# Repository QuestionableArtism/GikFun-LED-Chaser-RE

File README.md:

# GikFun-LED-Chaser-RE

### Purpose
I am testing to make sure my process of making schematic and then PCB and such is working.  I should be able to just use the solder practice kit 1:1 and it should work the same.

### Files:
The schematic, netlist, and PCB are all here.  I will update the ReadMe if it works.  I'm waiting on the order from osh park rn.

The one modification is that I am using a different power socket since the one they use is really obscure and I only found it in one place.  This one is meant to use the following receptacle:  https://www.mouser.com/ProductDetail/710-694106301002

Can be powered with any 2.1 x 5.5 5V DC barrel.

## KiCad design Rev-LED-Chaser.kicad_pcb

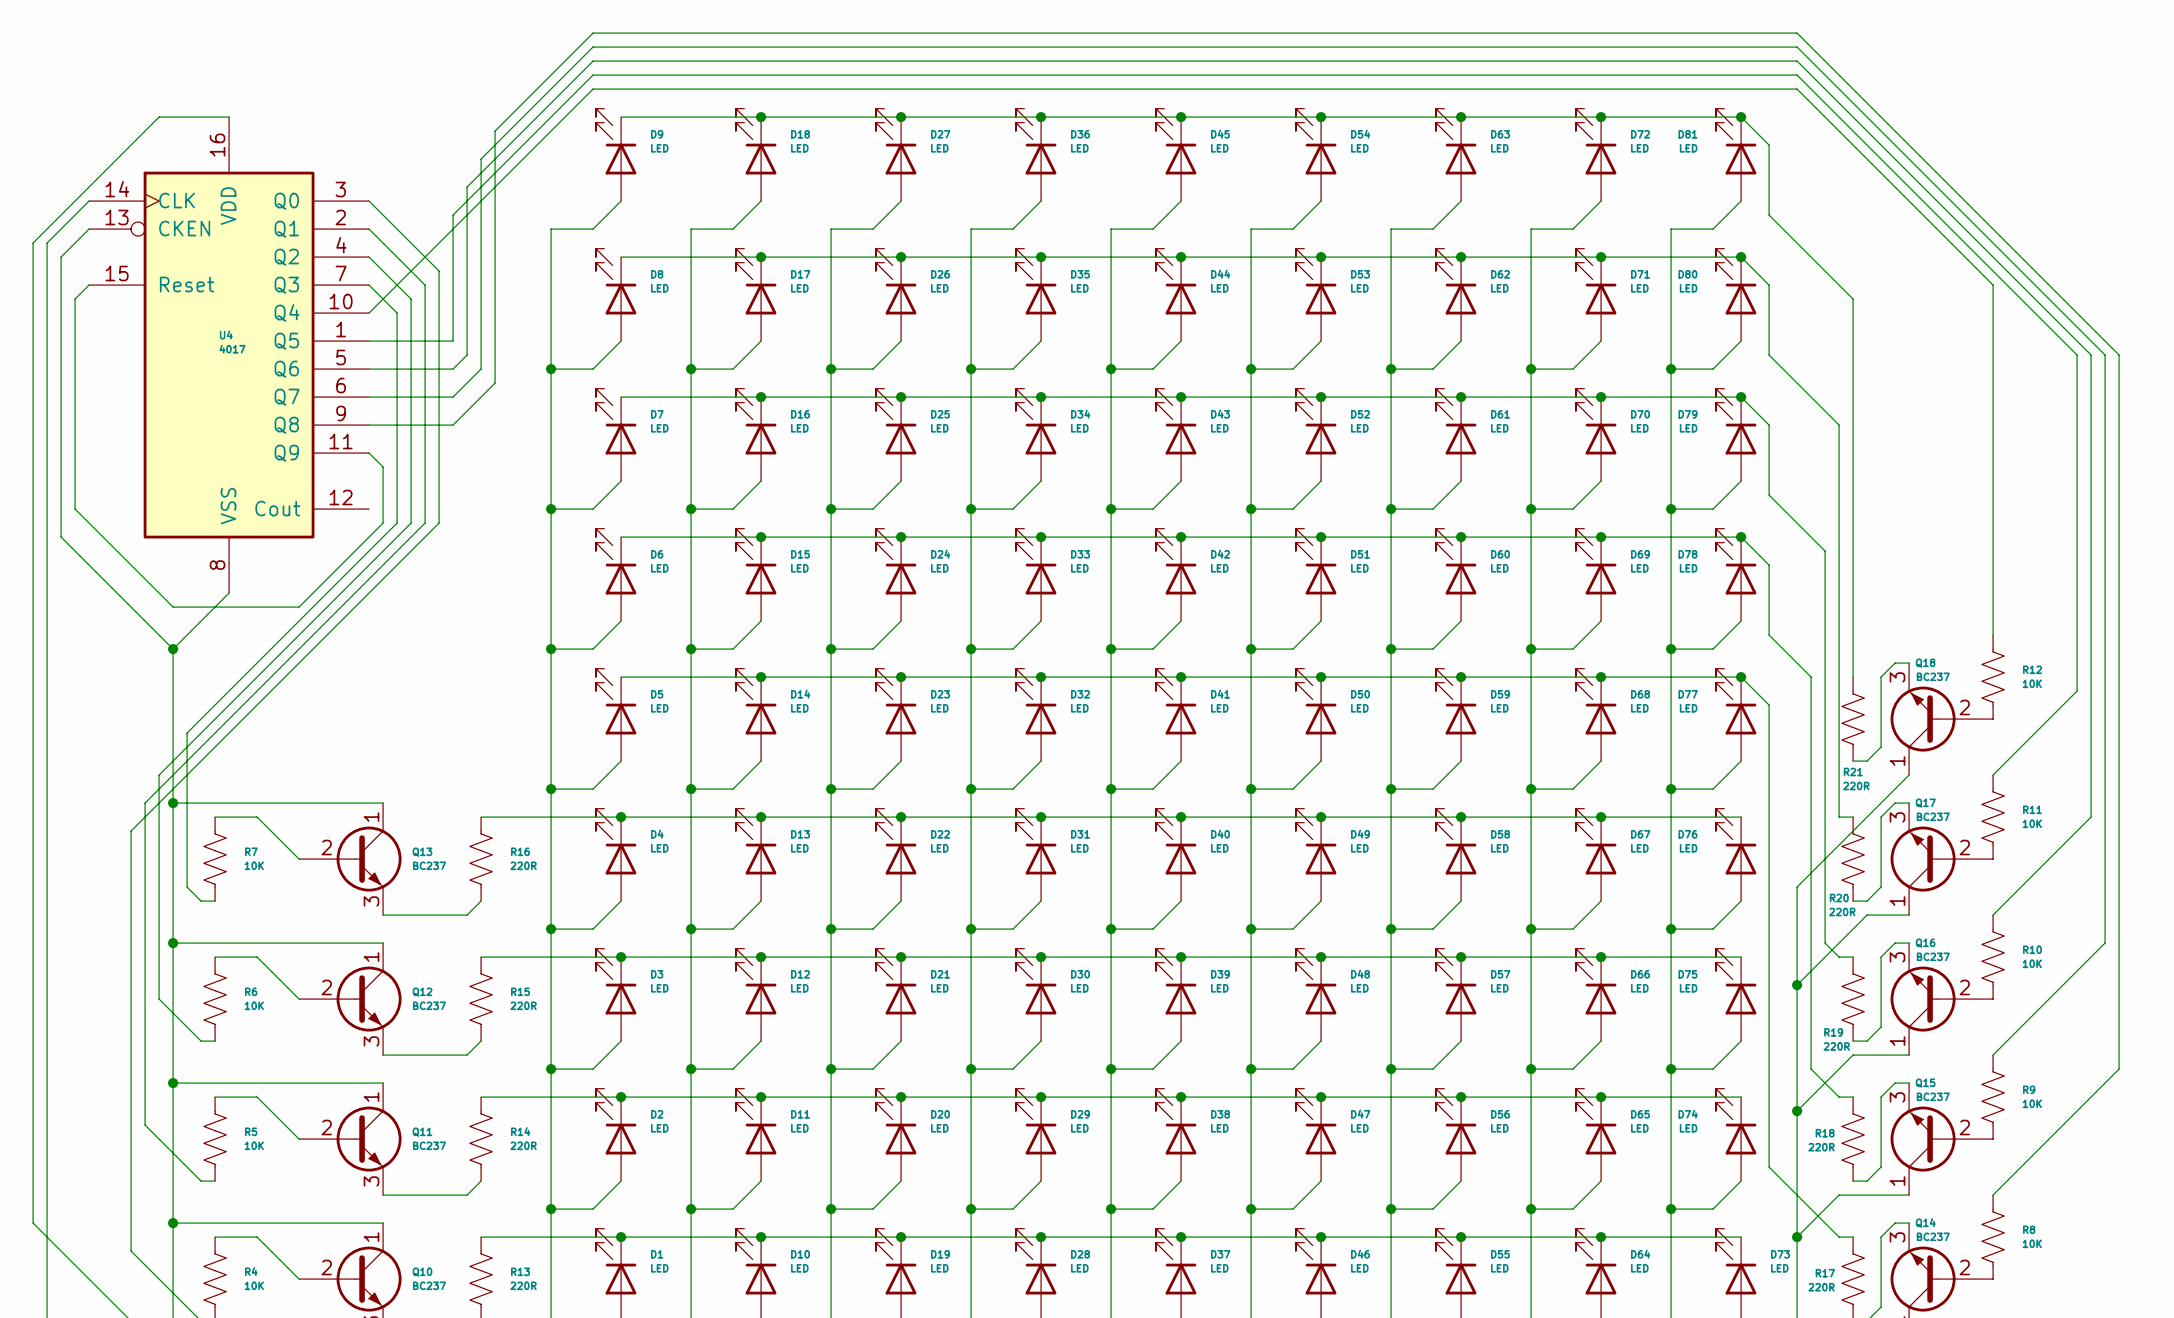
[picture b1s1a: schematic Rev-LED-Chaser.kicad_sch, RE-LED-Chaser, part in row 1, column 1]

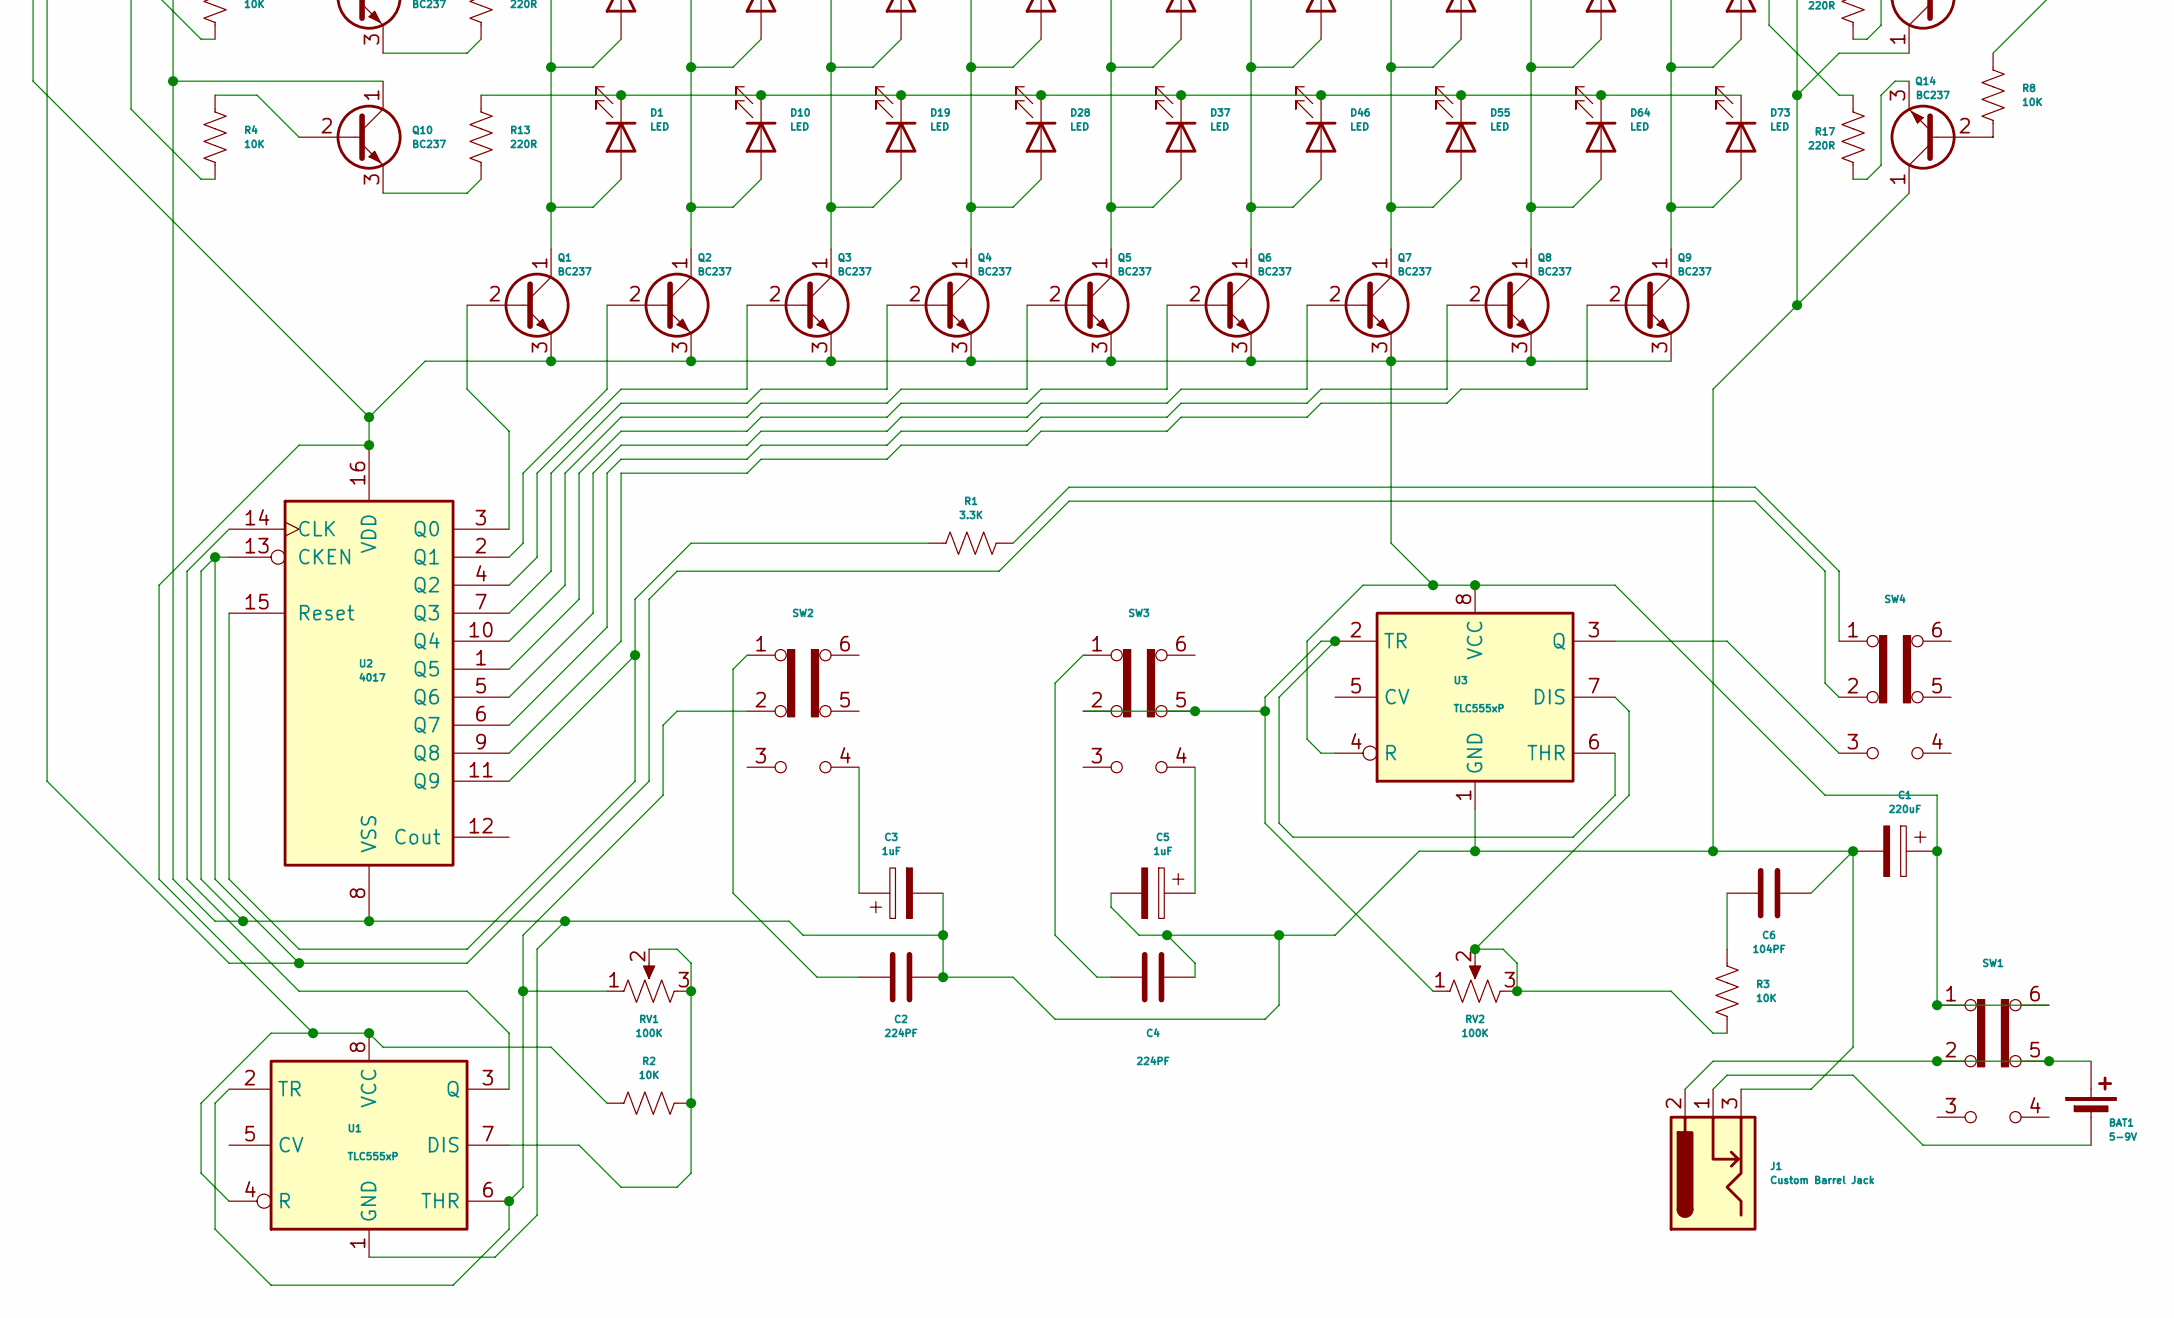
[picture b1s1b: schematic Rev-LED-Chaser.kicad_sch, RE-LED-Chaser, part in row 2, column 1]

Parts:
BAT1: 5-9V; LED_D4.0mm
C1: 220uF; CP_Radial_Horizontal
C2, C4: 224PF; C_Disc_D5.1mm_W3.2mm_P5.00mm
C3, C5: 1uF; CP_Radial_D4.0mm_P2.00mm
C6: 104PF; C_Disc_D5.0mm_W2.5mm_P2.50mm
D1, D2, D3, D4, D5, D6, D7, D8, D9, D10, D11, D12, D13, D14, D15, D16, D17, D18, D19, D20, D21, D22, D23, D24, D25, D26, D27, D28, D29, D30, D31, D32, D33, D34, D35, D36, D37, D38, D39, D40, D41, D42, D43, D44, D45, D46, D47, D48, D49, D50, D51, D52, D53, D54, D55, D56, D57, D58, D59, D60, D61, D62, D63, D64, D65, D66, D67, D68, D69, D70, D71, D72, D73, D74, D75, D76, D77, D78, D79, D80, D81: LED; LED_D5.0mm
J1: Custom Barrel Jack; BarrelJack_Wuerth_6941xx301002
Q1, Q2, Q3, Q4, Q5, Q6, Q7, Q8, Q9, Q10, Q11, Q12, Q13, Q14, Q15, Q16, Q17, Q18: BC237; TO-92_Inline
R1: 3.3K; R_Axial_DIN0207_L6.3mm_D2.5mm_P7.62mm_Horizontal
R2, R3, R4, R5, R6, R7, R8, R9, R10, R11, R12: 10K; R_Axial_DIN0207_L6.3mm_D2.5mm_P7.62mm_Horizontal
R13, R14, R15, R16, R17, R18, R19, R20, R21: 220R; R_Axial_DIN0207_L6.3mm_D2.5mm_P7.62mm_Horizontal
RV1, RV2: 100K; Potentiometer_Bourns_PTV09A-1_Single_Vertical
SW1, SW2, SW3, SW4: 807C Push Button 5.8mm x 5.8mm DPDT Switch
U1, U3: TLC555xP; DIP-8_W7.62mm
U2, U4: 4017; DIP-16_W7.62mm_LongPads

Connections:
unnamed: BAT1.1 (+), J1.2, SW1.2 (B), SW1.5 (B)
unnamed: BAT1.2 (-), J1.1
unnamed: C2.2, SW2.1 (A)
unnamed: C3.1, SW2.4 (A)
unnamed: C4.2, SW3.1 (A)
unnamed: C5.1, SW3.4 (A)
unnamed: C6.1, R3.2
unnamed: D1.2 (A), D2.2 (A), D3.2 (A), D4.2 (A), D5.2 (A), D6.2 (A), D7.2 (A), D8.2 (A), D9.2 (A), Q1.1 (C)
unnamed: D1.1 (K), D10.1 (K), D19.1 (K), D28.1 (K), D37.1 (K), D46.1 (K), D55.1 (K), D64.1 (K), D73.1 (K), R13.2
unnamed: D10.2 (A), D11.2 (A), D12.2 (A), D13.2 (A), D14.2 (A), D15.2 (A), D16.2 (A), D17.2 (A), D18.2 (A), Q2.1 (C)
unnamed: D2.1 (K), D11.1 (K), D20.1 (K), D29.1 (K), D38.1 (K), D47.1 (K), D56.1 (K), D65.1 (K), D74.1 (K), R14.2
unnamed: D3.1 (K), D12.1 (K), D21.1 (K), D30.1 (K), D39.1 (K), D48.1 (K), D57.1 (K), D66.1 (K), D75.1 (K), R15.2
unnamed: D4.1 (K), D13.1 (K), D22.1 (K), D31.1 (K), D40.1 (K), D49.1 (K), D58.1 (K), D67.1 (K), D76.1 (K), R16.2
unnamed: D5.1 (K), D14.1 (K), D23.1 (K), D32.1 (K), D41.1 (K), D50.1 (K), D59.1 (K), D68.1 (K), D77.1 (K), R17.2
unnamed: D6.1 (K), D15.1 (K), D24.1 (K), D33.1 (K), D42.1 (K), D51.1 (K), D60.1 (K), D69.1 (K), D78.1 (K), R18.2
unnamed: D7.1 (K), D16.1 (K), D25.1 (K), D34.1 (K), D43.1 (K), D52.1 (K), D61.1 (K), D70.1 (K), D79.1 (K), R19.2
unnamed: D8.1 (K), D17.1 (K), D26.1 (K), D35.1 (K), D44.1 (K), D53.1 (K), D62.1 (K), D71.1 (K), D80.1 (K), R20.2
unnamed: D9.1 (K), D18.1 (K), D27.1 (K), D36.1 (K), D45.1 (K), D54.1 (K), D63.1 (K), D72.1 (K), D81.1 (K), R21.2
unnamed: D19.2 (A), D20.2 (A), D21.2 (A), D22.2 (A), D23.2 (A), D24.2 (A), D25.2 (A), D26.2 (A), D27.2 (A), Q3.1 (C)
unnamed: D28.2 (A), D29.2 (A), D30.2 (A), D31.2 (A), D32.2 (A), D33.2 (A), D34.2 (A), D35.2 (A), D36.2 (A), Q4.1 (C)
unnamed: D37.2 (A), D38.2 (A), D39.2 (A), D40.2 (A), D41.2 (A), D42.2 (A), D43.2 (A), D44.2 (A), D45.2 (A), Q5.1 (C)
unnamed: D46.2 (A), D47.2 (A), D48.2 (A), D49.2 (A), D50.2 (A), D51.2 (A), D52.2 (A), D53.2 (A), D54.2 (A), Q6.1 (C)
unnamed: D55.2 (A), D56.2 (A), D57.2 (A), D58.2 (A), D59.2 (A), D60.2 (A), D61.2 (A), D62.2 (A), D63.2 (A), Q7.1 (C)
unnamed: D64.2 (A), D65.2 (A), D66.2 (A), D67.2 (A), D68.2 (A), D69.2 (A), D70.2 (A), D71.2 (A), D72.2 (A), Q8.1 (C)
unnamed: D73.2 (A), D74.2 (A), D75.2 (A), D76.2 (A), D77.2 (A), D78.2 (A), D79.2 (A), D80.2 (A), D81.2 (A), Q9.1 (C)
unnamed: Q1.2 (B), U2.3 (Q0)
unnamed: C1.1, Q1.3 (E), Q2.3 (E), Q3.3 (E), Q4.3 (E), Q5.3 (E), Q6.3 (E), Q7.3 (E), Q8.3 (E), Q9.3 (E), R2.1, SW1.1 (A), SW1.6 (C), U1.4 (R), U1.8 (VCC), U2.16 (VDD), U3.4 (R), U3.8 (VCC), U4.16 (VDD)
unnamed: Q2.2 (B), U2.2 (Q1)
unnamed: Q3.2 (B), U2.4 (Q2)
unnamed: Q4.2 (B), U2.7 (Q3)
unnamed: Q5.2 (B), U2.10 (Q4)
unnamed: Q6.2 (B), U2.1 (Q5)
unnamed: Q7.2 (B), U2.5 (Q6)
unnamed: Q8.2 (B), U2.6 (Q7)
unnamed: Q9.2 (B), U2.9 (Q8)
unnamed: Q10.2 (B), R4.2
unnamed: C1.2, C2.1, C3.2, C4.1, C5.2, C6.2, J1.3, Q10.1 (C), Q11.1 (C), Q12.1 (C), Q13.1 (C), Q14.1 (C), Q15.1 (C), Q16.1 (C), Q17.1 (C), Q18.1 (C), SW4.2 (B), U1.1 (GND), U2.8 (VSS), U2.13 (CKEN), U3.1 (GND), U4.8 (VSS), U4.13 (CKEN), U4.14 (CLK)
unnamed: Q10.3 (E), R13.1
unnamed: Q11.2 (B), R5.2
unnamed: Q11.3 (E), R14.1
unnamed: Q12.2 (B), R6.2
unnamed: Q12.3 (E), R15.1
unnamed: Q13.2 (B), R7.2
unnamed: Q13.3 (E), R16.1
unnamed: Q14.2 (B), R8.1
unnamed: Q14.3 (E), R17.1
unnamed: Q15.2 (B), R9.1
unnamed: Q15.3 (E), R18.1
unnamed: Q16.2 (B), R10.1
unnamed: Q16.3 (E), R19.1
unnamed: Q17.2 (B), R11.1
unnamed: Q17.3 (E), R20.1
unnamed: Q18.2 (B), R12.1
unnamed: Q18.3 (E), R21.1
unnamed: R1.2, SW4.1 (A)
unnamed: R2.2, RV1.2, RV1.3, U1.7 (DIS)
unnamed: U1.3 (Q), U2.14 (CLK)
unnamed: RV1.1, SW2.2 (B), U1.2 (TR), U1.6 (THR)
unnamed: R1.1, U2.11 (Q9), U2.15 (Reset)
unnamed: R3.1, RV2.2, RV2.3, U3.7 (DIS)
unnamed: SW4.3 (C), U3.3 (Q)
unnamed: RV2.1, SW3.2 (B), SW3.5 (B), U3.2 (TR), U3.6 (THR)
unnamed: R4.1, U4.3 (Q0)
unnamed: R5.1, U4.2 (Q1)
unnamed: R6.1, U4.4 (Q2)
unnamed: R7.1, U4.7 (Q3)
unnamed: R12.2, U4.10 (Q4)
unnamed: R11.2, U4.1 (Q5)
unnamed: R10.2, U4.5 (Q6)
unnamed: R9.2, U4.6 (Q7)
unnamed: R8.2, U4.9 (Q8)
unnamed: U4.11 (Q9), U4.15 (Reset)

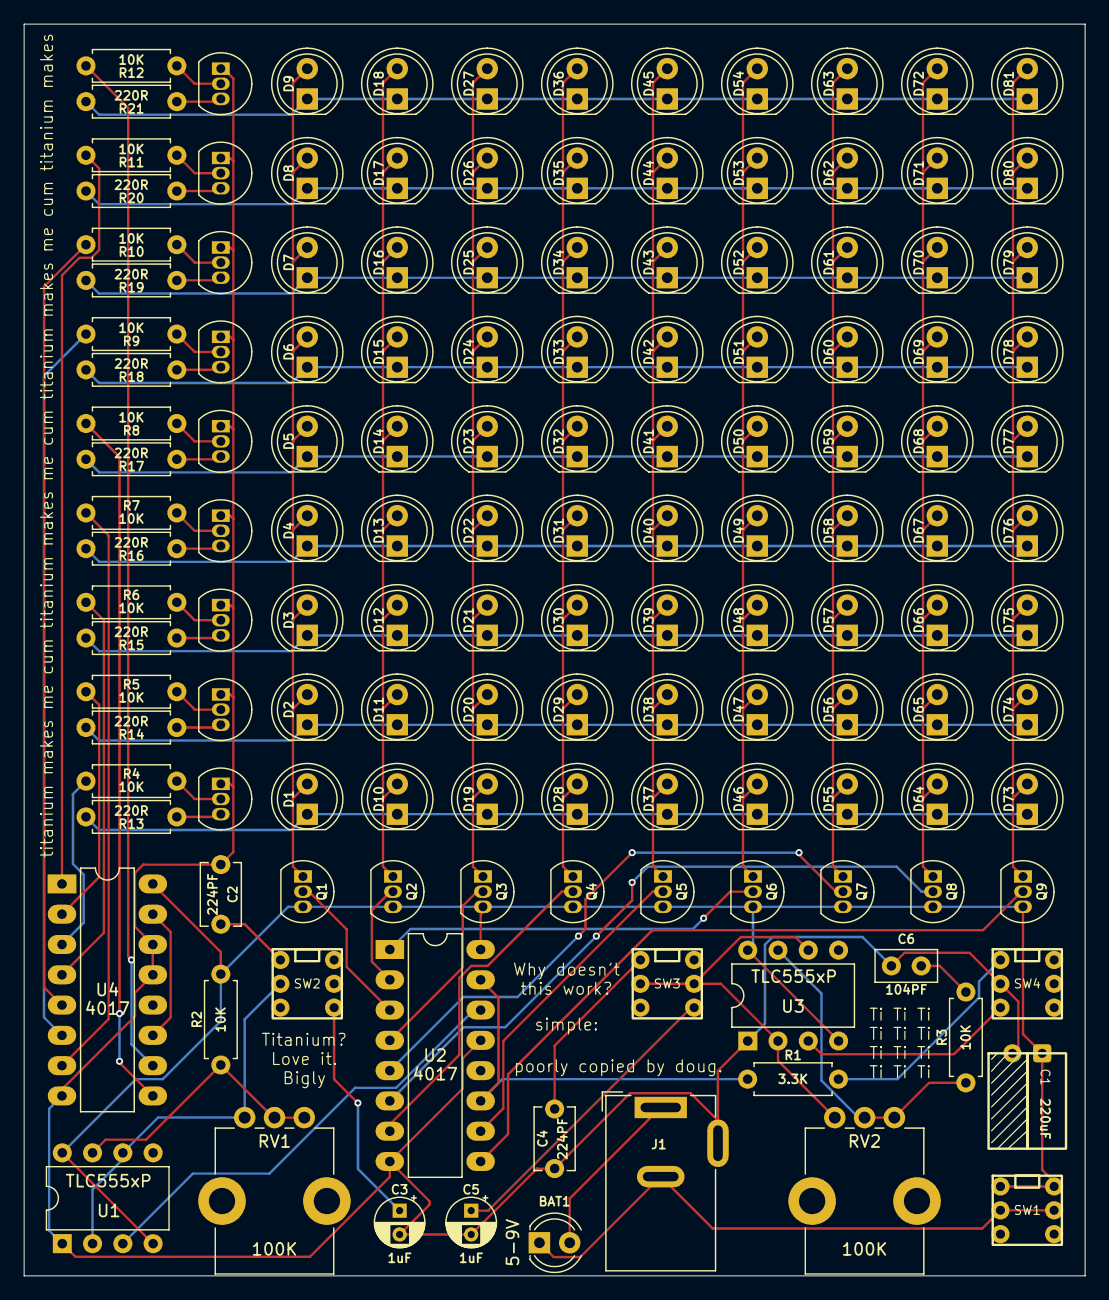
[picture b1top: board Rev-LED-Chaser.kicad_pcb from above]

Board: 2 copper layers, 89.0 x 105.0 mm, 138 parts (0 on the bottom side), 72 nets.

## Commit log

2024-10-11 initial
